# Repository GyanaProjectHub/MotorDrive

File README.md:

# MotorDrive
Trapezoidal, SPWM,SVPWM, Sensored Closed loop FOC

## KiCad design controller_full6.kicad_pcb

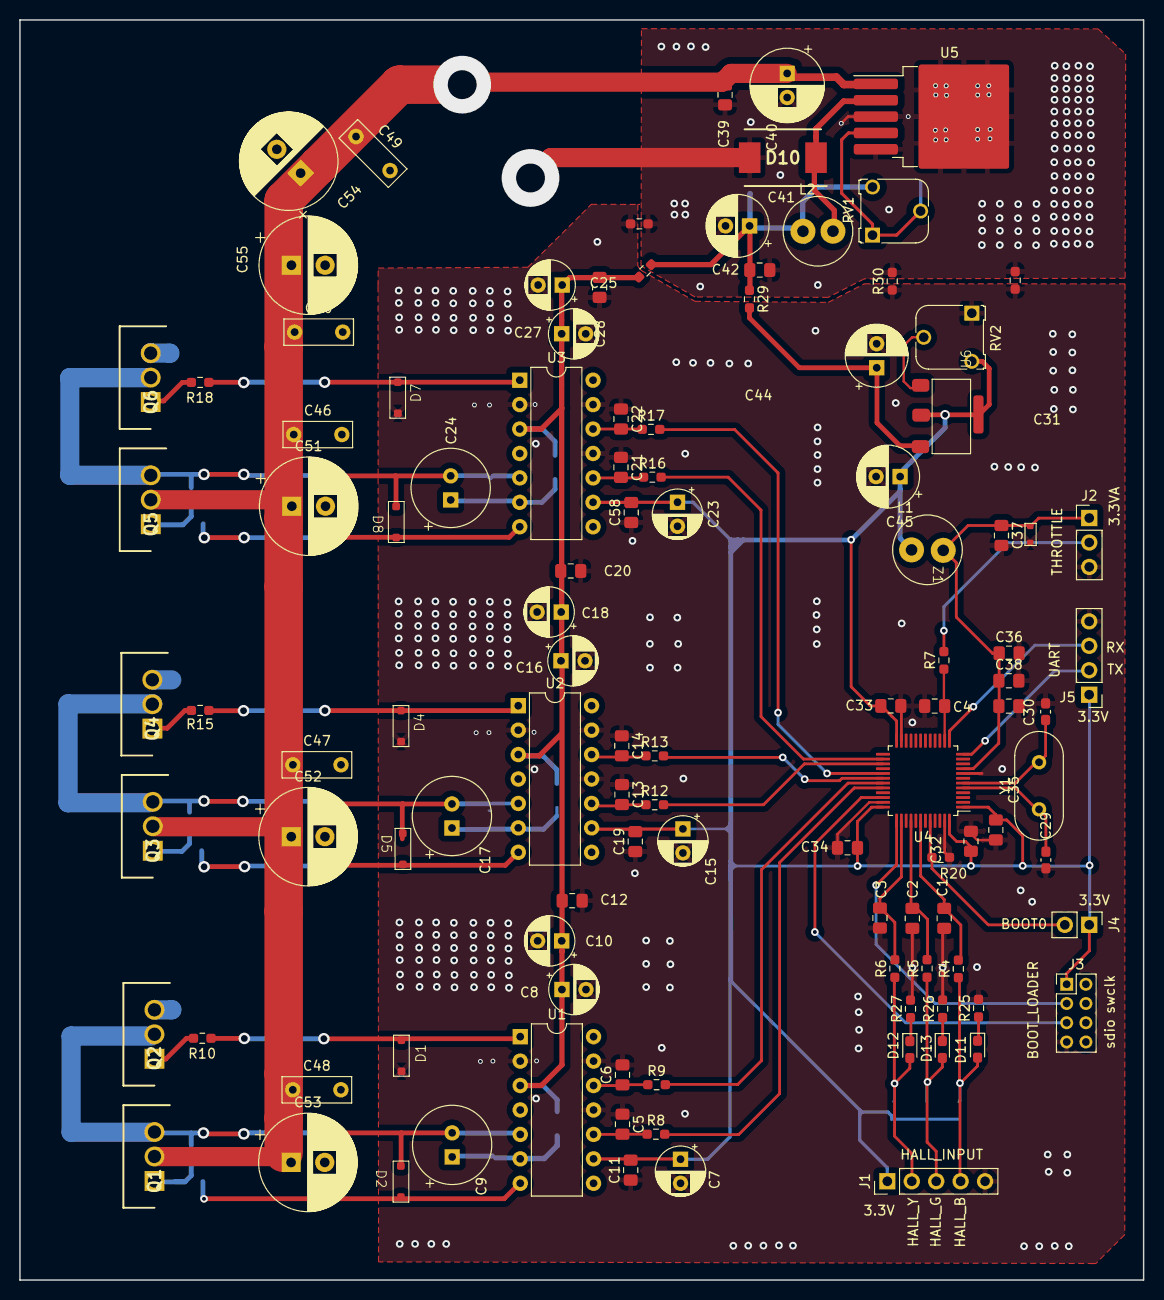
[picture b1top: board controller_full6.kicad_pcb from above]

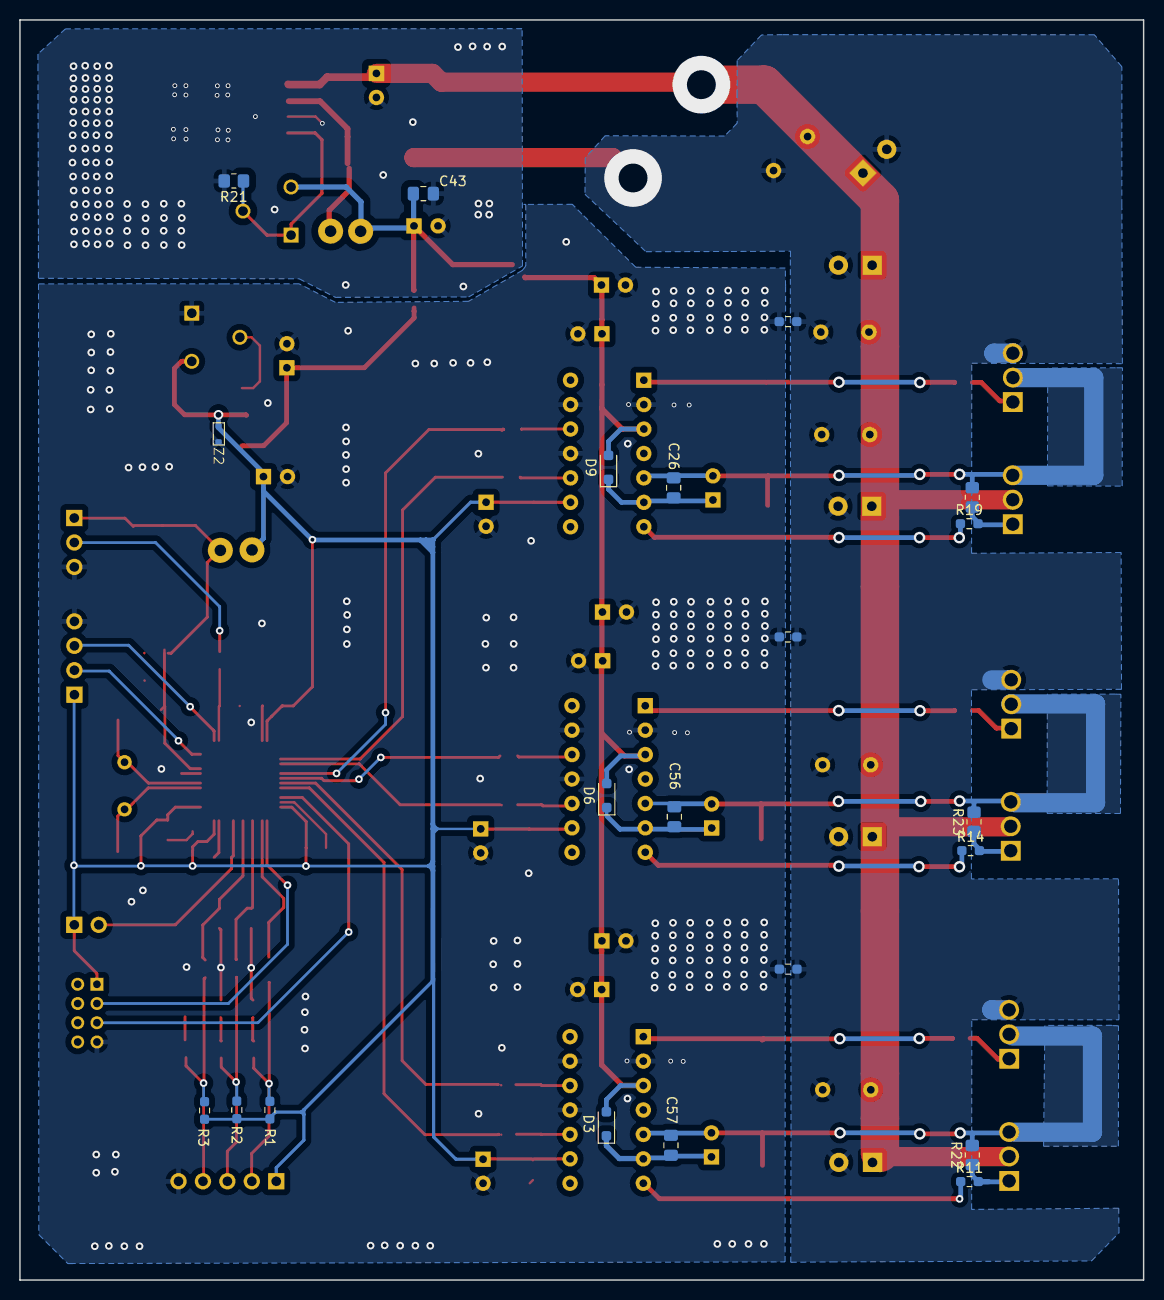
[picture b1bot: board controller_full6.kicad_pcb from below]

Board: 2 copper layers, 116.8 x 131.0 mm, 130 parts (21 on the bottom side), 56 nets.

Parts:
C1, C2, C3: 4.7nF; C_0805_2012Metric_Pad1.18x1.45mm_HandSolder
C4: 470nF; C_0805_2012Metric_Pad1.18x1.45mm_HandSolder
C5, C6, C13, C14, C21, C22: 470pF; C_0805_2012Metric_Pad1.18x1.45mm_HandSolder
C7, C8, C10, C15, C16, C18, C23, C25, C27: 4.7uF; CP_Radial_D5.0mm_P2.50mm
C9, C17, C24: 10uF; CP_Radial_Tantal_D8.0mm_P2.50mm
C11, C12, C19, C20, C26, C28, C39, C42, C56, C57, C58: 100nF; C_0805_2012Metric_Pad1.18x1.45mm_HandSolder
C29, C30: 30pF; C_0603_1608Metric_Pad1.08x0.95mm_HandSolder
C31, C32, C33, C34, C35, C38: 100pF; C_0805_2012Metric_Pad1.18x1.45mm_HandSolder
C36: 1u; C_0805_2012Metric_Pad1.18x1.45mm_HandSolder
C37: 100n; C_0805_2012Metric_Pad1.18x1.45mm_HandSolder
C40: 100uF; CP_Radial_D7.5mm_P2.50mm
C41, C45: 100uF; CP_Radial_D6.3mm_P2.50mm
C43: 4.7uF; C_0805_2012Metric_Pad1.18x1.45mm_HandSolder
C44: 10uF; CP_Radial_D6.3mm_P2.50mm
C46, C47, C48, C49, C50: 100nF; C_Rect_L7.0mm_W2.5mm_P5.00mm
C51, C52, C53, C54, C55: 470uF; CP_Radial_D10.0mm_P3.50mm
D1, D2, D4, D5, D7, D8: D_Zener; 1N4148_zener_diode
D3, D6, D9: SS18; D_SOD-323_HandSoldering
D10: 1N5822; DIOM8059X256N
D11, D12, D13: LED; D_0603_1608Metric_Pad1.05x0.95mm_HandSolder
J1: Conn_01x05; PinHeader_1x05_P2.54mm_Vertical
J2: Conn_01x03; PinHeader_1x03_P2.54mm_Vertical
J3: Conn_01x04; PinHeader_2x04_P2.00mm_Vertical
J4: Conn_01x02; PinHeader_1x02_P2.54mm_Vertical
J5: Conn_01x04; PinHeader_1x04_P2.54mm_Vertical
L1: 27n; L_Radial_D7.0mm_P3.00mm
L2: 100uH; L_Radial_D7.0mm_P3.00mm
Q1, Q2, Q3, Q4, Q5, Q6: IRF1407PBF; TO254P483X1016X1994-3P
R1, R2, R3, R20: 10k; R_0603_1608Metric_Pad0.98x0.95mm_HandSolder
R4, R5, R6: 3.3k; R_0603_1608Metric_Pad0.98x0.95mm_HandSolder
R7, R8, R9, R12, R13, R16, R17: 4.7k; R_0603_1608Metric_Pad0.98x0.95mm_HandSolder
R10, R11, R14, R15, R18, R19: 15; R_0603_1608Metric_Pad0.98x0.95mm_HandSolder
R21: 1.2k; R_0805_2012Metric_Pad1.20x1.40mm_HandSolder
R22, R23, R24: 15k; R_0805_2012Metric_Pad1.20x1.40mm_HandSolder
R25, R26, R27: 50; R_0603_1608Metric_Pad0.98x0.95mm_HandSolder
R28, R29, R30, R31, R32, R33, R34, R35: R; R_0603_1608Metric_Pad0.98x0.95mm_HandSolder
RV1: 47k; Potentiometer_Runtron_RM-065_Vertical
RV2: 10k; Potentiometer_Runtron_RM-065_Vertical
U1, U2, U3: IR2110; DIP-14_W7.62mm
U4: STM32F103C8Tx; LQFP-48_7x7mm_P0.5mm
U5: LM2576HVS-ADJ; TO-263-5_TabPin3
U6: LM1117S-ADJ; 1117s_ADJ
Y1: 8MHz; Crystal_HC18-U_Vertical
Z1, Z2: 1N4728A; MM3Z3V3T1G

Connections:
+3.3V: C7.1, C11.2, C15.1, C19.2, C23.1, C32.2, C33.2, C34.2, C35.2, C45.1, C58.2, J1.1, J3.1, J4.1, J5.1, L1.1, R1.2, R2.2, R3.2, RV2.3, U1.9 (VDD), U2.9 (VDD), U3.9 (VDD), U4.1 (VBAT), U4.24 (VDD), U4.36 (VDD), U4.48 (VDD), U6.2 (VO), Z2.1
+3.3VA: C31.1, C36.1, C37.1, C38.1, J2.1, L1.2, U4.9 (VDDA), Z1.1
+12V: C8.1, C10.1, C12.1, C16.1, C18.1, C20.1, C25.1, C27.1, C28.1, C41.1, C42.1, C43.1, C44.1, D3.2, D6.2, D9.2, L2.2, R29.1, R29.2, R32.1, R32.2, RV1.3, U1.3 (VCC), U2.3 (VCC), U3.3 (VCC), U6.3 (VI)
+48V: C39.1, C40.1, C46.1, C47.1, C48.1, C49.1, C50.1, C51.1, C52.1, C53.1, C54.1, C55.1, Q1.2 (D), Q3.2 (D), Q5.2 (D), U5.1 (VIN)
/Gate_Driver_1/HO_A: D2.1 (K), R11.1, U1.7 (HO)
/Gate_Driver_1/LO_A: D1.1 (K), R10.1, U1.1 (LO)
/Gate_Driver_2/HO_B: D5.1 (K), R14.1, U2.7 (HO)
/Gate_Driver_2/LO_B: D4.1 (K), R15.1, U2.1 (LO)
/Gate_Driver_3/HO_C: D8.1 (K), R19.1, U3.7 (HO)
/Gate_Driver_3/LO_C: D7.1 (K), R18.1, U3.1 (LO)
/Power_Circuit/GHA: Q1.1 (G), R11.2, R22.1
/Power_Circuit/GHB: Q3.1 (G), R14.2, R23.1
/Power_Circuit/GHC: Q5.1 (G), R19.2, R24.1
/Power_Circuit/GLA: Q2.1 (G), R10.2
/Power_Circuit/GLB: Q4.1 (G), R15.2
/Power_Circuit/GLC: Q6.1 (G), R18.2
/THROTTLE: C4.2, R7.1, U4.14 (PA4)
/hall_b: C1.1, R4.2, U4.42 (PB6)
/hall_g: C2.1, R5.2, U4.40 (PB4)
/hall_y: C3.1, R6.2, U4.38 (PA15)
/sdio: J3.5, U4.34 (PA13)
/stm32f103/Gha: R8.2, U4.32 (PA11)
/stm32f103/Ghb: R12.2, U4.27 (PB14)
/stm32f103/Ghc: R16.2, U4.26 (PB13)
/stm32f103/Gla: R9.2, U4.31 (PA10)
/stm32f103/Glb: R13.2, U4.30 (PA9)
/stm32f103/Glc: R17.2, U4.29 (PA8)
/stm32f103/RX: J5.3, U4.13 (PA3)
/stm32f103/TX: J5.2, U4.12 (PA2)
/swclk: J3.3, U4.37 (PA14)
GND: C1.2, C2.2, C3.2, C4.1, C5.1, C6.2, C7.2, C8.2, C10.2, C11.1, C12.2, C13.1, C14.1, C15.2, C16.2, C18.2, C19.1, C20.2, C21.1, C22.1, C23.2, C25.2, C27.2, C28.2, C29.2, C30.2, C31.2, C32.1, C33.1, C34.1, C35.1, C36.2, C37.2, C38.2, C39.2, C40.2, C41.2, C42.2, C43.2, C44.2, C45.2, C46.2, C47.2, C48.2, C49.2, C50.2, C51.2, C52.2, C53.2, C54.2, C55.2, C58.1, D1.2 (A), D4.2 (A), D7.2 (A), D10.2 (A), J1.5, J2.3, J3.7, J5.4, Q2.3 (S), Q4.3 (S), Q6.3 (S), R20.2, R21.2, R25.2, R26.2, R27.2, R28.1, R28.2, R30.1, R30.2, R31.1, R31.2, R33.1, R33.2, R34.1, R34.2, R35.1, R35.2, RV2.1, U1.2 (COM), U1.11 (SD), U1.13 (VSS), U2.2 (COM), U2.11 (SD), U2.13 (VSS), U3.2 (COM), U3.11 (SD), U3.13 (VSS), U4.8 (VSSA), U4.23 (VSS), U4.35 (VSS), U4.47 (VSS), U5.3 (GND), U5.5 (~ON/OFF), Z1.2, Z2.2
unnamed: D10.1 (K), L2.1, U5.2 (OUT)
unnamed: D11.2 (A), J1.4, R3.1, R4.1
unnamed: D11.1 (K), R25.1
unnamed: D12.2 (A), J1.2, R1.1, R6.1
unnamed: D12.1 (K), R27.1
unnamed: D13.2 (A), J1.3, R2.1, R5.1
unnamed: D13.1 (K), R26.1
unnamed: J2.2, R7.2
unnamed: J4.2, R20.1, U4.44 (BOOT0)
unnamed: C5.2, R8.1, U1.10 (HIN)
unnamed: C6.1, R9.1, U1.12 (LIN)
unnamed: C9.1, C57.2, D3.1, U1.6 (VB)
unnamed: C13.2, R12.1, U2.10 (HIN)
unnamed: C14.2, R13.1, U2.12 (LIN)
unnamed: C17.1, C56.1, D6.1, U2.6 (VB)
unnamed: C21.2, R16.1, U3.10 (HIN)
unnamed: C22.2, R17.1, U3.12 (LIN)
unnamed: C24.1, C26.1, D9.1, U3.6 (VB)
unnamed: C29.1, U4.5 (PD0), Y1.1
unnamed: C30.1, U4.6 (PD1), Y1.2
unnamed: R21.1, RV1.1, RV1.2, U5.4 (FB)
unnamed: RV2.2, U6.1 (ADJ)
phase_a: C9.2, C57.1, D2.2 (A), Q1.3 (S), Q2.2 (D), R22.2, U1.5 (VS)
phase_b: C17.2, C56.2, D5.2 (A), Q3.3 (S), Q4.2 (D), R23.2, U2.5 (VS)
phase_c: C24.2, C26.2, D8.2 (A), Q5.3 (S), Q6.2 (D), R24.2, U3.5 (VS)

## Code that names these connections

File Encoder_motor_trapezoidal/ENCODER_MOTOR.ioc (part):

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Mcu.Name=STM32F103C(8-B)Tx
Mcu.Package=LQFP48
Mcu.UserName=STM32F103C8Tx
PA10.GPIOParameters=GPIO_Label
PA10.GPIO_Label=gla
PA10.Signal=GPIO_Output
PA11.GPIOParameters=GPIO_Label
PA11.GPIO_Label=gha
PA11.Signal=S_TIM1_CH4
PA13.Mode=Serial_Wire
PA13.Signal=SYS_JTMS-SWDIO
PA14.Mode=Serial_Wire
PA14.Signal=SYS_JTCK-SWCLK
PA15.GPIOParameters=GPIO_PuPd,GPIO_Label
PA15.GPIO_Label=I
PA15.GPIO_PuPd=GPIO_PULLUP
PA15.Signal=GPXTI15
PA2.GPIOParameters=GPIO_PuPd,GPIO_Label
PA2.GPIO_Label=A_clone
PA2.GPIO_PuPd=GPIO_PULLUP
PA2.Signal=GPXTI2
PA3.GPIOParameters=GPIO_PuPd,GPIO_Label
PA3.GPIO_Label=I_clone
PA3.GPIO_PuPd=GPIO_PULLUP
PA3.Signal=GPXTI3
PA4.GPIOParameters=GPIO_Label
PA4.GPIO_Label=throttle
PA4.Signal=ADCx_IN4
PA8.GPIOParameters=GPIO_Label
PA8.GPIO_Label=glc
PA8.Signal=GPIO_Output
PA9.GPIOParameters=GPIO_Label
PA9.GPIO_Label=glb
PA9.Signal=GPIO_Output
PB13.GPIOParameters=GPIO_Label
PB13.GPIO_Label=ghc
PB13.Mode=PWM Generation1 CH1N
PB13.Signal=TIM1_CH1N
PB14.GPIOParameters=GPIO_Label
PB14.GPIO_Label=ghb
PB14.Mode=PWM Generation2 CH2N
PB14.Signal=TIM1_CH2N
PB4.GPIOParameters=GPIO_PuPd,GPIO_Label,GPIO_ModeDefaultEXTI
PB4.GPIO_Label=B
PB4.GPIO_ModeDefaultEXTI=GPIO_MODE_IT_RISING
PB4.GPIO_PuPd=GPIO_PULLUP
PB4.Signal=GPXTI4
PB6.GPIOParameters=GPIO_PuPd,GPIO_Label
PB6.GPIO_Label=A
PB6.GPIO_PuPd=GPIO_PULLUP
PB6.Signal=GPXTI6
PD0-OSC_IN.Mode=HSE-External-Oscillator
PD0-OSC_IN.Signal=RCC_OSC_IN
PD1-OSC_OUT.Mode=HSE-External-Oscillator
PD1-OSC_OUT.Signal=RCC_OSC_OUT
RCC.SYSCLKFreq_VALUE=64000000
RCC.SYSCLKSource=RCC_SYSCLKSOURCE_PLLCLK
board=custom
